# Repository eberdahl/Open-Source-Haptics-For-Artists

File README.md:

Open-Source-Haptics-For-Artists
-------------------------------
This website provides a venue for users to share open-source software and hardware haptic technology with one another. While the focus is primarily on artistic applications, we believe that mutual collaboration can help the field of haptics progress most rapidly in art, science, and technology. 

This git repository has been created via a collaboration between the Technical University of Berlin, the Cardiff School of Art & Design, and Stanford University.  If you develop some nice contributions, please let us know, and we would be happy to incorporate them.

Current maintainers:
Edgar Berdahl (eberdahl@ccrma.stanford.edu)
and
Alexandros Kontogeorgakopoulos (akontogeorgakopoulos@cardiffmet.ac.uk)

Main website:
http://www.openhaptics.org/

To use OSHA, install git and then run the following command:

git clone --recursive https://github.com/eberdahl/Open-Source-Haptics-For-Artists.git

cd Open-Source-Haptics-For-Artists

To update this repository, run the following from the root directory:

git pull

git submodule update

In general, please use the Google group for asking questions:
https://groups.google.com/group/open-source-haptics-for-artists

I have decided to officially support the Max/MSP objects and the Synth-A-Modeler objects, once I deliver them.  I STRONGLY RECOMMEND USING MAX/MSP OR SYNTH-A-MODELER.  However, I understand that people might be interested in using the older pd or Chai3D code, so I am including the source for them as starter code.

Notes on software
-----------------
- Currently the Max/MSP support is the most fleshed out, including testing the concept of using capacitive sensing to enable or disable the force feedback.  To use the Max/MSP patches, you will to put the palette folder in the path.
!!!**  Remember to set the "Signal Vector Size" to 1  **!!!

Notes on hardware
-----------------
By default the motor controller sets up 
- D4: Direction control of Motor A 
- D5: PWM speed control of Motor A 
- D6: PWM speed control of Motor B 
- D7: Direction control of Motor B 
- A0: Current sense of Motor A 
- A1: Current sense of Motor B 

So pin D5 and D6 on Arduino are ATMega328 pins correspond to
D5 --> PD5(T1)
D6 --> PD6(AIN0)

Best,
Edgar Berdahl
March, 2012 and updated July, 2012 and October, 2012

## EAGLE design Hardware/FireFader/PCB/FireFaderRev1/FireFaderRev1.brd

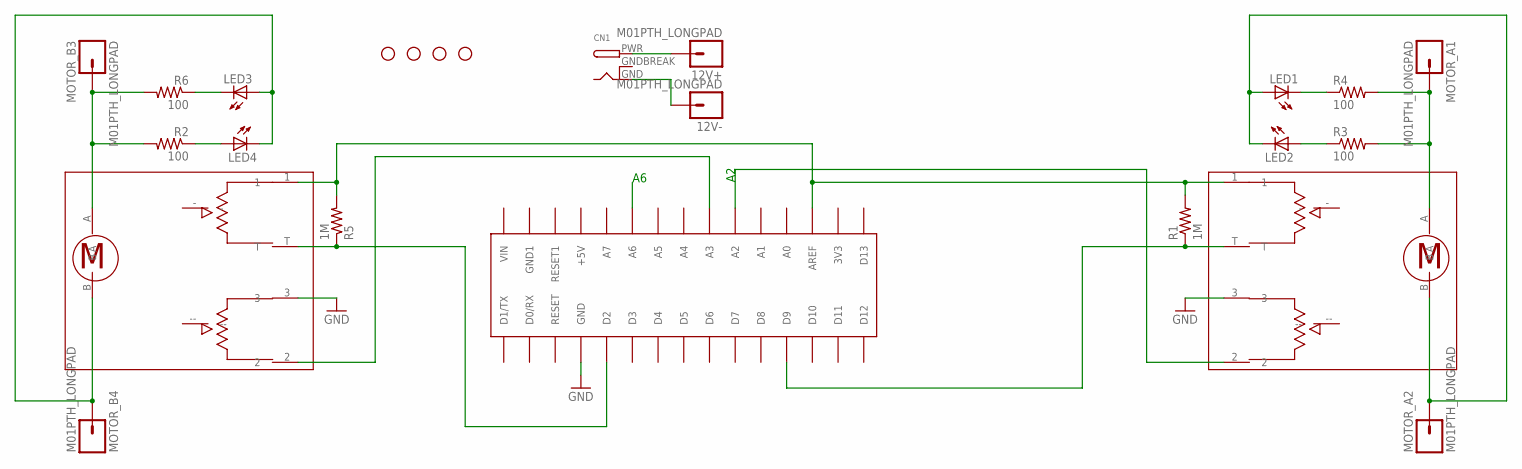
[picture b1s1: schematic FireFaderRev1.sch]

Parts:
12V+, 12V-: M01PTH_LONGPAD; 1X01_LONGPAD
CN1: DCBARRELPTH; DCJACK_2MM_PTH
LED1, LED2, LED3, LED4: LED5MM
MOTOR_A1, MOTOR_A2: M01PTH_LONGPAD; 1X01_LONGPAD
MOTOR_B3, MOTOR_B4: M01PTH_LONGPAD; 1X01_LONGPAD
R1, R5: 1M; AXIAL-0.4
R2, R3, R4, R6: 100; AXIAL-0.6
STANDOFF1, STANDOFF2, STANDOFF3, STANDOFF4: STAND-OFF
U$1: ARDUINONANO; PDIP-32
U$2, U$3: ALPS-RSA0N11M9A07; MF-MOTORFADER-ALPS

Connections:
A1: U$1.A3, U$3.2
A2: U$1.A2, U$2.2
A6: U$1.A6
AREF: R1.P$2 (2), R5.P$2 (2), U$1.AREF, U$2.1, U$3.1
GND: U$1.GND, U$2.3, U$3.3
GNDBREAK: CN1.GNDBREAK
MA1: MOTOR_A1.1, R3.P$2 (2), R4.P$2 (2), U$2.A
MA2: LED1.A, LED2.K (C), MOTOR_A2.1, U$2.B
MB3: MOTOR_B3.1, R2.P$2 (2), R6.P$2 (2), U$3.A
MB4: LED3.A, LED4.K (C), MOTOR_B4.1, U$3.B
unnamed: LED2.A, R3.P$1 (1)
unnamed: LED1.K (C), R4.P$1 (1)
unnamed: R1.P$1 (1), U$1.D9, U$2.T
unnamed: 12V-.1, CN1.GND
unnamed: 12V+.1, CN1.PWR
unnamed: R5.P$1 (1), U$1.D2, U$3.T
unnamed: LED4.A, R2.P$1 (1)
unnamed: LED3.K (C), R6.P$1 (1)

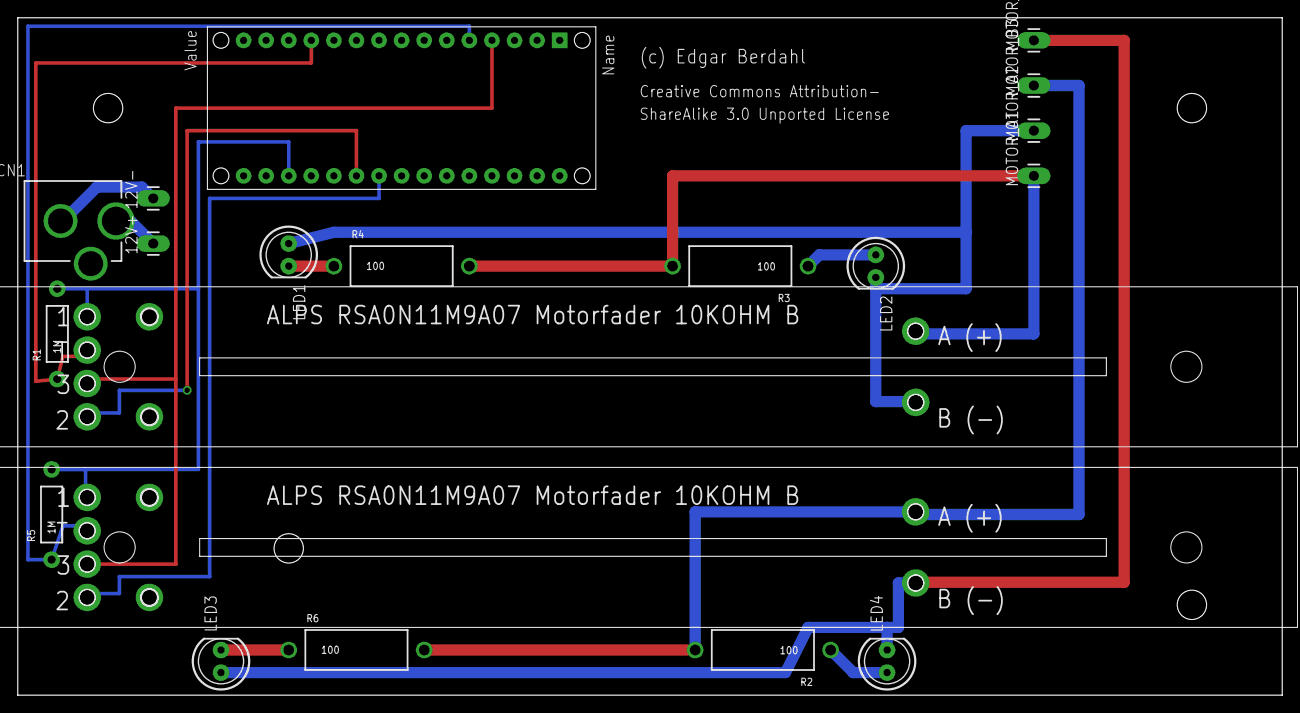
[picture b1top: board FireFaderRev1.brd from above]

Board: 2 copper layers, 142.2 x 76.2 mm, 24 parts (0 on the bottom side), 16 nets.

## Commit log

2012-07-12 Put the files online for the first time.
    In the later releases, I will sort the files better to make it more clear which parts are supported and which parts are not.
2012-10-04 Changes to v1.0 include - cleaned up the code and made it more presentable - made sure that all of the 1-channel versions of the code were compatible - made sure that all of the 1-channel versions of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
2013-06-04 Basically reorganized and reuploaded the entire repository with support for the FireFader.
2013-07-08 Updated link~ object
2013-07-08 Updated SaM submodule
2014-02-28 Updating repo after long time
2014-02-28 Edgar's update for the NIME 2014 conference. Still waiting for Alexandros' update.
2014-02-28 Updating software
2014-02-28 Updated name from MaxMSP to Max.
2014-02-28 I guess I made some changes here.
2014-06-29 Adding some nice models and removing a less nice model.
2014-06-29 Adding detent models for FireFader
2014-06-29 Moving patches around.
2014-06-29 Adding in other patches that we cleaned up some more today.
2014-08-31 Improved the setting of the initial conditions of mass~
2014-08-31 Adapted the implementation of mass~ better to how Max operates
2014-10-28 Updated read me to help users figure out how make sure the correct serial port is being addressed.
2014-11-04 Rotary device
2014-11-04 Updating readme
2014-11-04 Updated notes
2014-11-04 nicer
2014-11-04 Small details
2014-11-05 Changed default haptic effect for the slider to make it more obvious what it's doing.
2014-11-05 Added an IIR lowpass filter to the pot on the fader to reduce the motor noise.
2015-05-22 Updating SaM submodule (and a few various changes)
2015-07-14 I added a text file
2015-07-14 deleted the notesAlexandros
2015-08-26 Needed extra space
2015-10-03 Made instructions more detailed
2015-10-05 Adding support for Bill Verplanks device
2016-04-10 Updated to work with Pd vanilla
2016-04-10 Updating notes
2016-07-01 Added firmware for version with two motors attached
2016-10-15 Convert the counters to mycounter2 for latest greatest non-extended pd
2016-12-17 Updates from workshop at McGill
2016-12-17 This was renamed
2016-12-17 Made note explaining updates
2017-01-22 Fixed tmp files
2017-01-22 Fixed part number
2017-01-24 Made homework assignemnts a little bit more clear

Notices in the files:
Hardware/FireFader/PCB/FireFaderRev1/FireFaderRev1.brd:
Creative Commons Attribution-
parts and their libraries:
SparkFun-Connectors: Licensing: CC v3.0 Share-Alike You are welcome to use this library for commercial purposes.
